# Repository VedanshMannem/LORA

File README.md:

# LoRa puck
This project's goal is to make my own LoRa (long rage) puck. It can transmit RF (radio frequency) signals and this board also comes with a 4 pin connector to attach outside sensors. The ultimate purpose of this board is to learn more about RF circuits and logic as well as create a module for transmission. 

## Some takeaways
This is one of my first full scale PCB projects. I found this one extremely fun because I got to learn a lot more about RF circuits, some of the physics behind managing these electronics, and it was just great practice overall to improve my schematics and PCB routing. This was also my first time working with multi-layer PCBs, and the whole via concept was really cool to connect gnd across different layers. Until now, this has definitely been my best hardware project!

## Usage
This repo contains KiCAD project files as well as photos showing the finished project (schematics, 2D & 3D layout JLCPCB final version, etc.). The included BOM contains a full cost breakdown of all necessary components. Some components aren't in stock currently, so a few subsitutes were used. A lot of them also require extended assembly, slightly increasing the cost of the PCB. I have a few substitutes to my BOM already listed, but I think it's price optimized especially considering all the specific modules required for this project. 

## Some photos:

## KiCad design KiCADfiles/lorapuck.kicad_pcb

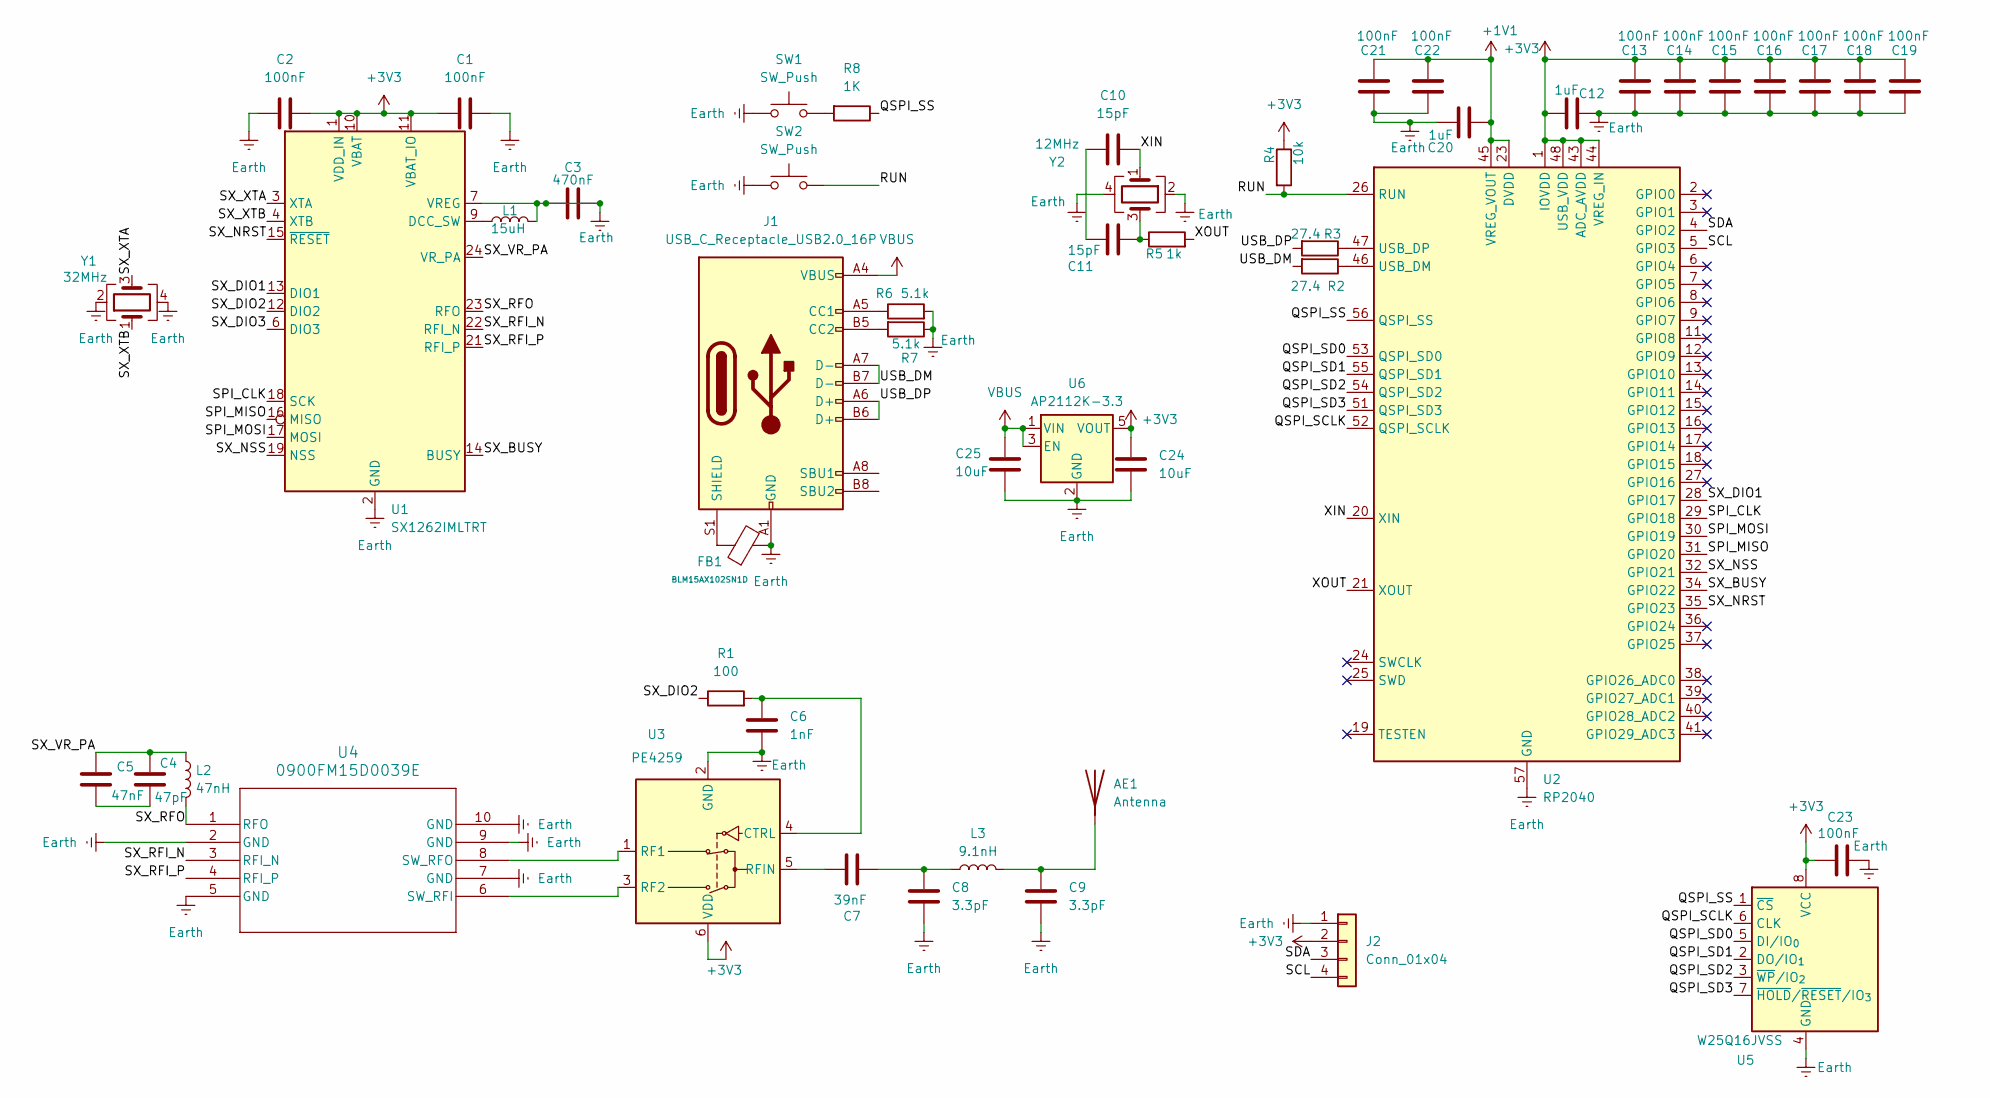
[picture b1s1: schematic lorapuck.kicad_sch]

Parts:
AE1: Antenna; PinSocket_1x01_P2.54mm_Vertical
C1, C2, C13, C14, C15, C16, C17, C18, C19, C21, C22, C23: 100nF; C_0402_1005Metric
C3: 470nF; C_0402_1005Metric
C4: 47pF; C_0402_1005Metric
C5: 47nF; C_0402_1005Metric
C6: 1nF; C_0402_1005Metric
C7: 39nF; C_0402_1005Metric
C8, C9: 3.3pF; C_0402_1005Metric
C10, C11: 15pF; C_0402_1005Metric
C12, C20: 1uF; C_0402_1005Metric
C24, C25: 10uF; C_0402_1005Metric
FB1: BLM15AX102SN1D; FB_0603; Current Rating 2A; Tolerance ±25%; Part BLM18PG121SN1D; LCSC C14709
J1: USB_C_Receptacle_USB2.0_16P; USB_C_Receptacle_GCT_USB4105-xx-A_16P_TopMnt_Horizontal
J2: Conn_01x04; PinSocket_1x04_P2.54mm_Vertical
L1: 15uH; L_0402_1005Metric
L2: 47nH; L_0402_1005Metric
L3: 9.1nH; L_0402_1005Metric
R1: 100; R_0402_1005Metric
R2, R3: 27.4; R_0402_1005Metric
R4: 10k; R_0402_1005Metric
R5: 1k; R_0402_1005Metric
R6, R7: 5.1k; R_0402_1005Metric
R8: 1K; R_0402_1005Metric
SW1, SW2: SW_Push; SW_Tactile_SPST_NO_Straight_CK_PTS636Sx25SMTRLFS
U1: SX1262IMLTRT; QFN-24-1EP_4x4mm_P0.5mm_EP2.6x2.6mm
U2: RP2040; QFN-56-1EP_7x7mm_P0.4mm_EP3.2x3.2mm
U3: PE4259; SOT-363_SC-70-6
U4: 0900FM15D0039E; 0900FM15D0039E_JOT
U5: W25Q16JVSS; SOIC-8_5.3x5.3mm_P1.27mm
U6: AP2112K-3.3; SOT-23-5
Y1: 32MHz; Crystal_SMD_3225-4Pin_3.2x2.5mm
Y2: 12MHz; Crystal_SMD_Abracon_ABM8G-4Pin_3.2x2.5mm

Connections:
+1V1: C20.2, C21.1, C22.1, U2.23 (DVDD), U2.45 (VREG_VOUT), U2.50 (DVDD)
+3V3: C1.1, C2.2, C12.1, C13.1, C14.1, C15.1, C16.1, C17.1, C18.1, C19.1, C23.1, C24.1, J2.2, R4.1, U1.1 (VDD_IN), U1.10 (VBAT), U1.11 (VBAT_IO), U2.1 (IOVDD), U2.10 (IOVDD), U2.22 (IOVDD), U2.33 (IOVDD), U2.42 (IOVDD), U2.43 (ADC_AVDD), U2.44 (VREG_IN), U2.48 (USB_VDD), U2.49 (IOVDD), U3.6 (VDD), U5.8 (VCC), U6.5 (VOUT)
/QSPI_SCLK: U2.52 (QSPI_SCLK), U5.6 (CLK)
/QSPI_SD0: U2.53 (QSPI_SD0), U5.5 (DI/IO_{0})
/QSPI_SD1: U2.55 (QSPI_SD1), U5.2 (DO/IO_{1})
/QSPI_SD2: U2.54 (QSPI_SD2), U5.3 (~WP/IO_{2})
/QSPI_SD3: U2.51 (QSPI_SD3), U5.7 (~HOLD/~RESET/IO_{3})
/QSPI_SS: R8.1, U2.56 (QSPI_SS), U5.1 (~CS)
/RUN: R4.2, SW2.2, U2.26 (RUN)
/SCL: J2.4, U2.5 (GPIO3)
/SDA: J2.3, U2.4 (GPIO2)
/SPI_CLK: U1.18 (SCK), U2.29 (GPIO18)
/SPI_MISO: U1.16 (MISO), U2.31 (GPIO20)
/SPI_MOSI: U1.17 (MOSI), U2.30 (GPIO19)
/SX_BUSY: U1.14 (BUSY), U2.34 (GPIO22)
/SX_DIO1: U1.13 (DIO1), U2.28 (GPIO17)
/SX_DIO2: R1.1, U1.12 (DIO2)
/SX_DIO3: U1.6 (DIO3)
/SX_NRST: U1.15 (~RESET), U2.35 (GPIO23)
/SX_NSS: U1.19 (NSS), U2.32 (GPIO21)
/SX_RFI_N: U1.22 (RFI_N), U4.3 (RFI_N)
/SX_RFI_P: U1.21 (RFI_P), U4.4 (RFI_P)
/SX_RFO: L2.2, U1.23 (RFO), U4.1 (RFO)
/SX_VR_PA: C4.1, C5.1, L2.1, U1.24 (VR_PA)
/SX_XTA: U1.3 (XTA), Y1.3
/SX_XTB: U1.4 (XTB), Y1.1
/USB_DM: J1.A7 (D-), J1.B7 (D-), R2.2
/USB_DP: J1.A6 (D+), J1.B6 (D+), R3.2
/XIN: C10.2, U2.20 (XIN), Y2.1
/XOUT: R5.2, U2.21 (XOUT)
unnamed: AE1.1 (A), C9.1, L3.2
unnamed: C4.2, C5.2
unnamed: C7.2, C8.1, L3.1
unnamed: C10.1, C11.1
unnamed: C11.2, R5.1, Y2.3
unnamed: J1.A5 (CC1), R6.1
unnamed: J1.B5 (CC2), R7.2
unnamed: FB1.1, J1.S1 (SHIELD)
unnamed: R8.2, SW1.2
unnamed: L1.1, U1.9 (DCC_SW)
unnamed: R2.1, U2.46 (USB_DM)
unnamed: R3.1, U2.47 (USB_DP)
unnamed: C6.1, R1.2, U3.4 (CTRL)
unnamed: U3.1 (RF1), U4.8 (SW_RFO)
unnamed: U3.3 (RF2), U4.6 (SW_RFI)
unnamed: C7.1, U3.5 (RFIN)
VBUS: C25.1, J1.A4 (VBUS), J1.A9 (VBUS), J1.B4 (VBUS), J1.B9 (VBUS), U6.1 (VIN), U6.3 (EN)

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
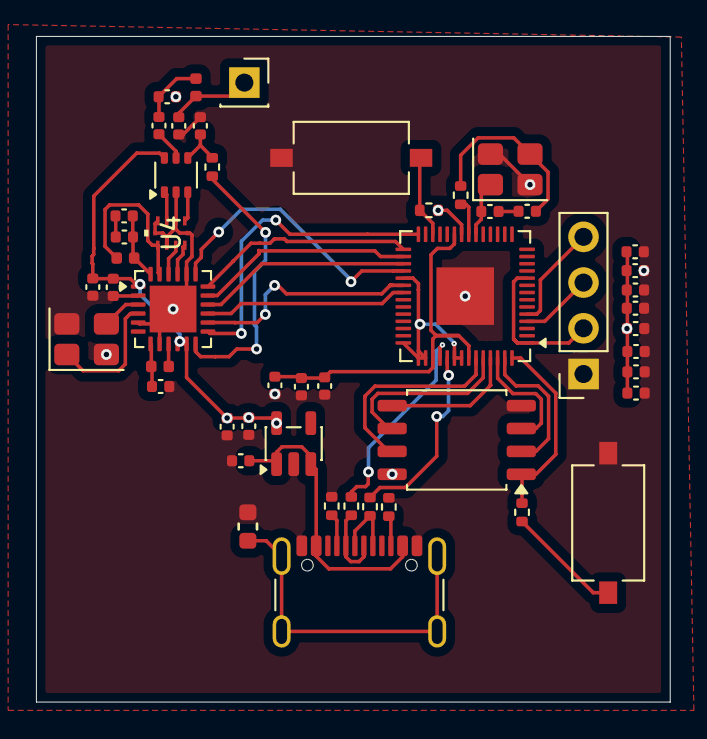
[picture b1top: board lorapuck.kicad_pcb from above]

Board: 4 copper layers, 35.2 x 37.0 mm, 50 parts (0 on the bottom side), 48 nets.

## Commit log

2025-11-29 Update placeholder.txt with new content
2025-11-29 kicad files
2025-11-29 Create p
2025-11-29 Add README content for Lora puck project
    Added project description and images for the Lora puck.
2025-11-29 Correct description of hardware project status
2025-11-30 Revise README with project details and insights
    Updated project description and added sections for takeaways and usage.
2025-11-30 Enhance usage section with BOM details and substitutes
    Expanded the usage section to include information about BOM substitutes and cost optimization.
